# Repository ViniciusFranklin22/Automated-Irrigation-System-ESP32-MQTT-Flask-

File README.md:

# 🌿 Smart Irrigation System with ESP32 and IoT

This project was developed for real-time plant monitoring and automatic irrigation using ESP32, MQTT, and a web-based interface.

## 🚀 Features

- 📡 Real-time monitoring:
  - Soil moisture
  - Temperature
  - Air humidity
  - Light intensity

- 💧 Irrigation:
  - Manual (via web button)
  - Automatic (based on soil moisture threshold)

- ⚙️ Remote configuration:
  - Minimum soil moisture threshold
  - Minimum interval between irrigations
  - Pump activation time
  - Enable/disable automatic mode
  - Configuration is stored in ESP32 non-volatile memory, ensuring persistence after reboot

- 💡 System status indicators:
  - LED indicator for Wi-Fi connection status  
  - LED indicator for MQTT connection status  
  - Provides quick visual feedback for system debugging and reliability

- 📊 Web dashboard:
  - Historical graphs (24h, 48h, 1 week)
  - Device online/offline status
  - Last irrigation timestamp
  - Real data collected over several days
  - Clear visualization of sensor behavior, including soil moisture variation after irrigation events

## 🧠 Architecture

ESP32 → MQTT → Backend (Flask) → Web Dashboard  
ESP32 ← MQTT ← Backend (Flask) ← Web Dashboard  

- ESP32 publishes sensor data via MQTT  
- Backend stores data in CSV files using Pandas  
- Web interface consumes data through a Flask API  
- Commands are sent to the ESP32 via MQTT  

## 🛠️ Technologies Used

- Python (Flask, Pandas)  
- MQTT (paho-mqtt)  
- ESP32 (Arduino framework)  
- HTML + Bootstrap + Chart.js  
- KiCad  

## 🔌 Hardware Implementation

- Prototype built using a breadboard for data acquisition and testing  
- Sensors and ESP32 connected for real-world measurements  
- System validated with real environmental data over multiple days  

## 🧩 PCB Design

- Custom PCB designed using KiCad  
- Developed aiming toward a future product-ready solution  

## 📷 Interface

## ▶️ How to Run

1. Configure your MQTT broker  
2. Adjust file paths in the code  
3. Run the data collection scripts:
   - `server_get_msg.py`
   - `server_get_msg_irrig.py`
4. Start the Flask application:
   ```bash
   python main_flask.py

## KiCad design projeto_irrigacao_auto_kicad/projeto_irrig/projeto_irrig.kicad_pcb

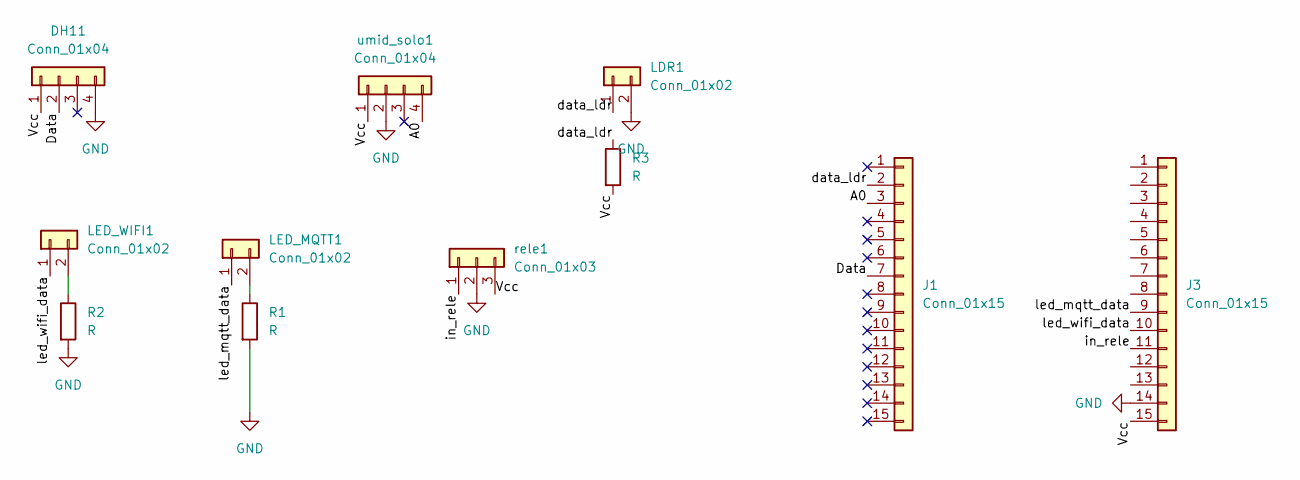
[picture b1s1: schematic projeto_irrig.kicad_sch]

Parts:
DH11: Conn_01x04; PinHeader_1x04_P2.54mm_Vertical
J1, J3: Conn_01x15; PinHeader_1x15_P2.54mm_Vertical
LDR1: Conn_01x02; PinHeader_1x02_P2.54mm_Vertical
LED_MQTT1: Conn_01x02; PinHeader_1x02_P2.54mm_Vertical
LED_WIFI1: Conn_01x02; PinHeader_1x02_P2.54mm_Vertical
R1, R2, R3: R; R_Axial_DIN0207_L6.3mm_D2.5mm_P7.62mm_Horizontal
rele1: Conn_01x03; PinHeader_1x03_P2.54mm_Vertical
umid_solo1: Conn_01x04; PinHeader_1x04_P2.54mm_Vertical

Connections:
/A0: J1.3, umid_solo1.4
/Data: DH11.2, J1.7
/Vcc: DH11.1, J3.15, R3.2, rele1.3, umid_solo1.1
/data_ldr: J1.2, LDR1.1, R3.1
/in_rele: J3.11, rele1.1
/led_mqtt_data: J3.9, LED_MQTT1.1
/led_wifi_data: J3.10, LED_WIFI1.1
GND: DH11.4, J3.14, LDR1.2, R1.2, R2.2, rele1.2, umid_solo1.2
unnamed: LED_MQTT1.2, R1.1
unnamed: LED_WIFI1.2, R2.1

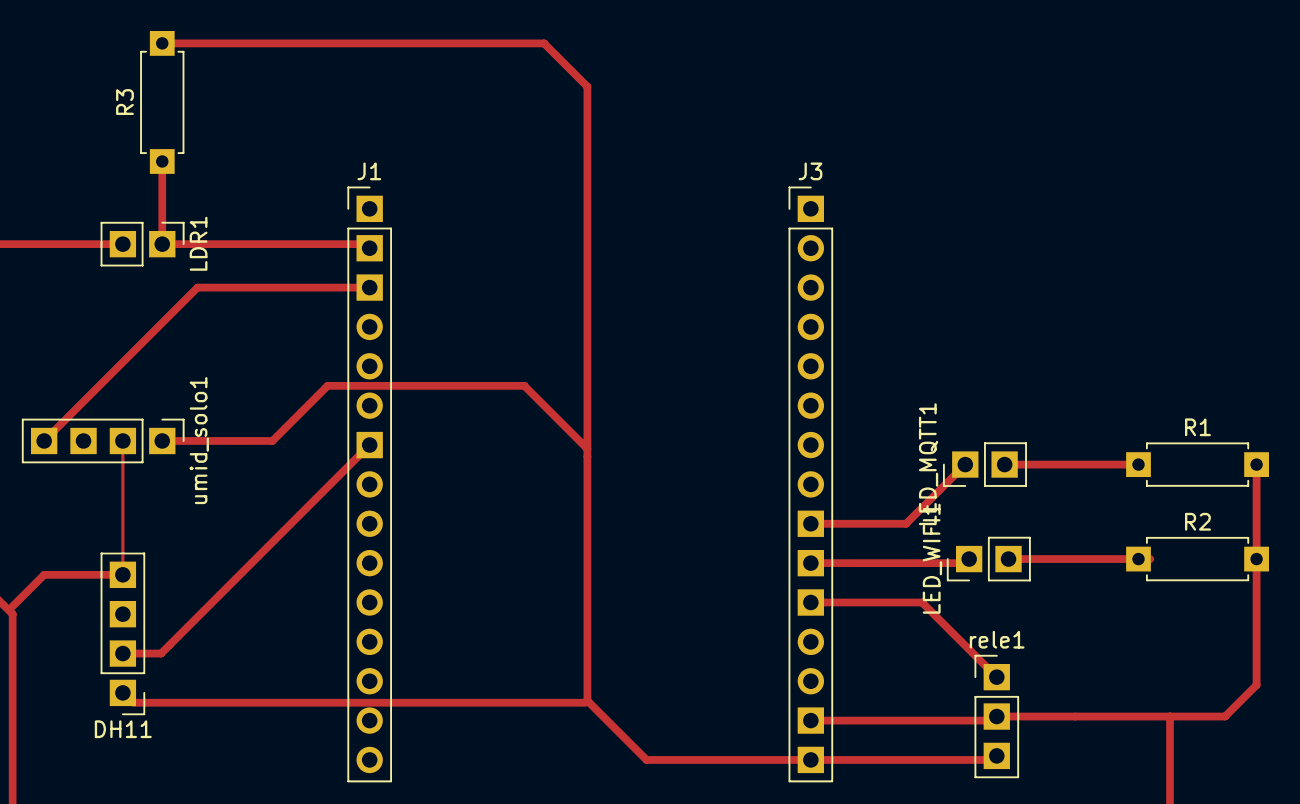
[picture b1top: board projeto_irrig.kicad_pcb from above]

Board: 2 copper layers, 11 parts (0 on the bottom side), 10 nets.
